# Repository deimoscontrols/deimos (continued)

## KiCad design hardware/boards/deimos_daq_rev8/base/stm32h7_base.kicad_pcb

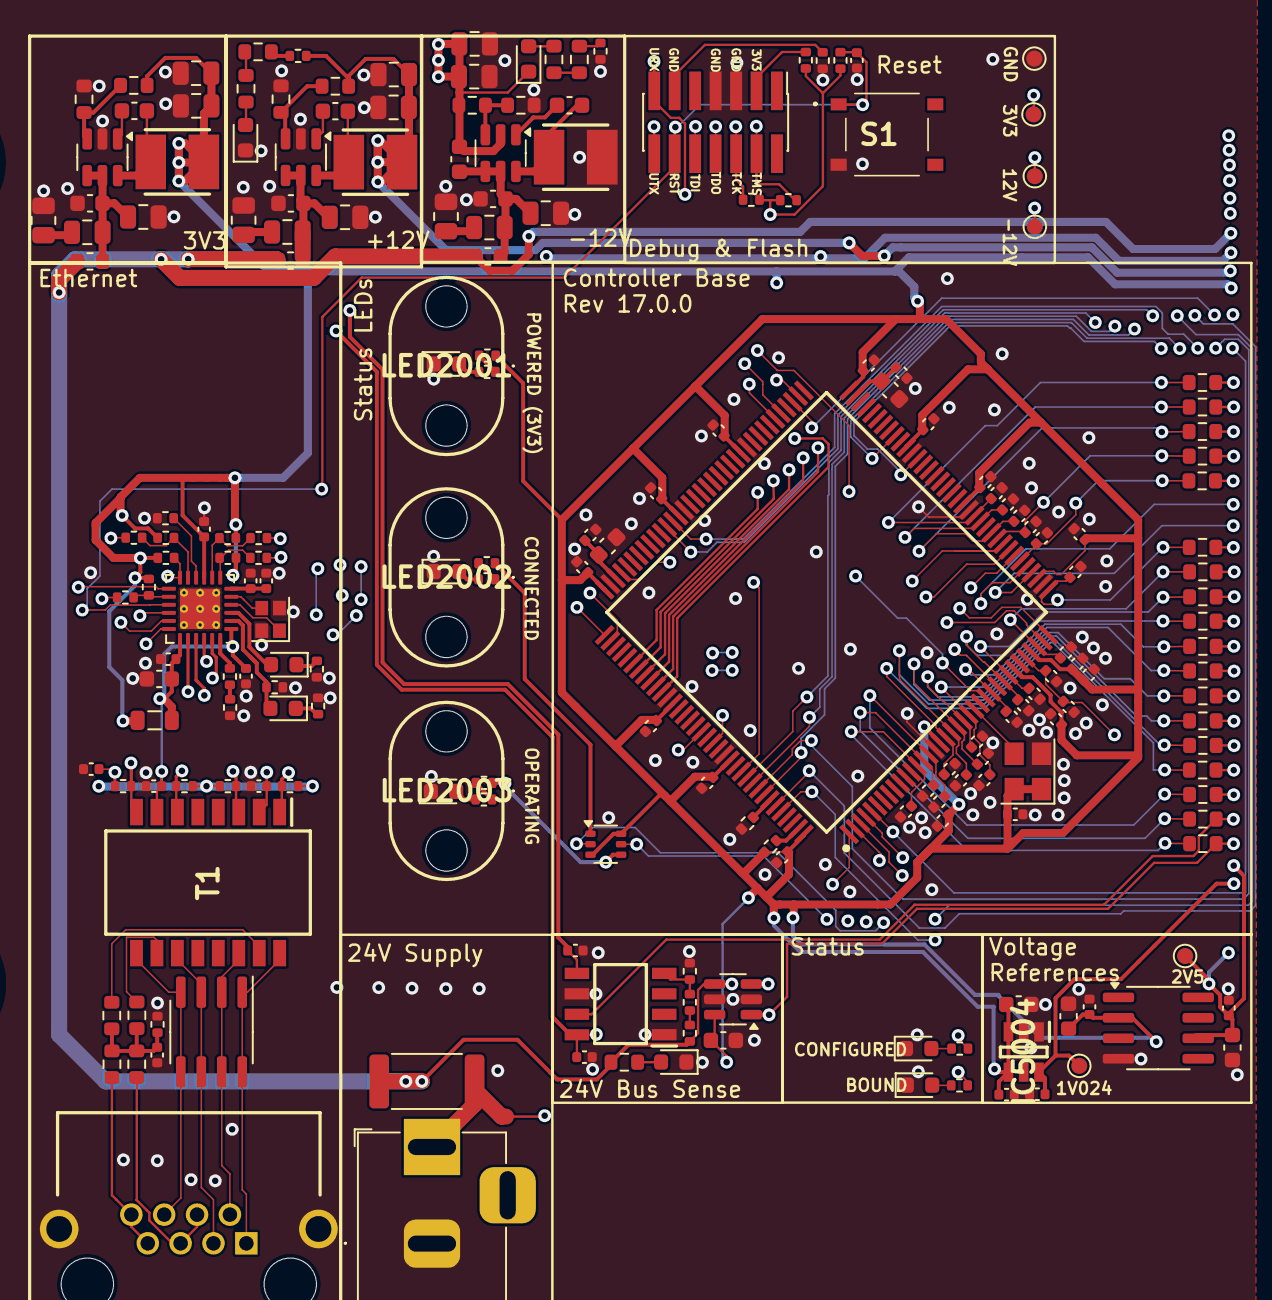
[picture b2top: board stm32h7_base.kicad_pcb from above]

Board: 4 copper layers, 202 parts (0 on the bottom side), 117 nets.

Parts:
C9, C10, C23, C5002, C5004, C6003: 10uF; C_0603_1608Metric
C11, C12, C13, C14, C15, C17, C18, C19, C22, C24, C26, C28, C29, C30, C31, C32, C33, C34, C35, C36, C37, C38, C39, C40, C4004, C5001, C5003, C5005, C6001, C6002: 0.1uF; C_0402_1005Metric
C16: 4.7nF; C_0402_1005Metric
C25: 470pF 0402; C_0402_1005Metric
C27, C44, C45, C46, C47, C48, C49, C50, C51, C52, C53, C54, C55, C56, C59, C60, C61, C62, C63: 1uF 0402; C_0402_1005Metric
C42, C43: 10nF; C_0402_1005Metric
C4001: 0.1uF 0603; C_0603_1608Metric
C4002, C4008, C4011, C7003, C9001, C9002, C10005: 0.1uF 50V 0603; C_0603_1608Metric
C4006, C4007, C4010, C7001, C7002, C7004, C9004, C10001, C10002: 10uF 50V 0805; C_0805_2012Metric
C4009, C9003, C10006: 2.2uF 50V 0805; C_0805_2012Metric
D2, D6, D36, D37, D38, D39, D2001, D2003, D2004, D2005: Purple LED; LED_0603_1608Metric
D5: CDNBS08-SLVU2.8-4; SOIC-8_3.9x4.9mm_P1.27mm
FB1: GZ2012D601TF; L_0805_2012Metric
H1001, H1002: MountingHole_for_10-32; MountingHole_5mm
IC1: STM32H743ZIT6; QFP50P2200X2200X160-144N
IC4001, IC10001, IC10002: TPS560430XDBVR; SOT-23-6
IC5004: REF35102QDBVR; SOT95P280X145-6N
IC8001: INA826AIDR; SOIC127P600X175-8N
J4: Conn_02x07_Odd_Even; PinHeader_2x07_P1.27mm_Vertical_SMD
J3001: RCH_RC01133; RCHRC01133
J8001: Barrel_Jack PJ-202BH; BarrelJack_Horizontal
L4001, L9001: 33uH FNR4020S330MT; INDPM4040X300N
L4002, L8001, L9002: 220nH 0603; L_0603_1608Metric
L7001: 12uH FNR4030S120MT; INDPM4040X300N
LED2001, LED2002, LED2003: SMFLP10.0; SMFLP100
R1, R2, R3, R4, R6, R27, R28, R29, R30, R31, R33, R49, R2007, R2008, R8006, R8007: 10k; R_0402_1005Metric
R5, R50: 1k; R_0402_1005Metric
R8, R9, R10, R11, R22, R32, R35, R36, R37, R38, R39, R40, R41, R44, R45, R46, R51, R52: 10R 0603; R_0603_1608Metric
R13, R14, R15, R16: 49.9; R_0402_1005Metric
R17, R18, R19, R20: 75; R_0603_1608Metric
R21: 1M; R_0402_1005Metric
R23, R26, R47, R48: 33R; R_0402_1005Metric
R34, R56, R8005: 1.5k; R_0402_1005Metric
R54: 12k; R_0402_1005Metric
R57: 100R; R_0402_1005Metric
R58, R2001, R2002, R2004, R2011, R2012, R2013, R2014: 100R 0402; R_0402_1005Metric
R2003, R4002, R9001: 243k 0603; R_0603_1608Metric
R2005, R2006, R2009, R2010, R4003, R9002, R10001: 22.1k 0603; R_0603_1608Metric
R4001, R10002, R10003: 1R 0805; R_0805_2012Metric
R7001: 51k 0603; R_0603_1608Metric
R8004: MRF6432(2512)LR006FTS 0.006 1%; R_2512_6332Metric
S1: TS-1187A-B-A-B; TS1187ABAB
T1: H1102NLT; SOIC127P940X622-16N
TP4001: TestPoint_GND_1; TestPoint_Pad_D1.0mm
TP10001, TP11001: TestPoint_+12V; TestPoint_Pad_D1.0mm
TP10003: TestPoint_+2V5; TestPoint_Pad_D1.0mm
TP10004: TestPoint_+3V3; TestPoint_Pad_D1.0mm
TP10005: TestPoint_+1V024; TestPoint_Pad_D1.0mm
U5: LAN8742A; VQFN-24-1EP_4x4mm_P0.5mm_EP2.5x2.5mm_ThermalVias
U2001: NTJD4001NT1G; SOT-363_SC-70-6
U4001: INA181A2; SOT-23-6
U6002: ADR4525; SOIC-8_3.9x4.9mm_P1.27mm
Y1: SiT1602BI-21-33S-48.000000; Crystal_SMD_3225-4Pin_3.2x2.5mm
Y2: NX2016SA-25.000M-STD-CZS-1; Crystal_SMD_2016-4Pin_2.0x1.6mm

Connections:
+1V024: C6001.1, IC5004.6 (VREF), TP10005.1
+2V5: C28.2, C43.2, C5003.2, C5004.2, IC1.32 (VREF+), TP10003.1, U6002.6 (OUT)
+3V3: C11.2, C12.2, C26.2, C29.2, C30.2, C31.2, C32.2, C33.2, C34.2, C35.2, C36.2, C37.2, C38.2, C39.2, C40.2, C42.2, C4001.1, C5001.2, C5002.2, C6002.2, C6003.2, C7004.1, C10006.1, FB1.1, IC1.17 (VDD_1), IC1.30 (VDD_2), IC1.33 (VDDA), IC1.39 (VDD_3), IC1.52 (VDD_4), IC1.62 (VDD_5), IC1.72 (VDD_6), IC1.84 (VDD_7), IC1.95 (VDD33USB), IC1.108 (VDD_8), IC1.121 (VDD_9), IC1.131 (VDD_10), IC1.144 (VDD_11), IC5004.3 (EN), IC5004.4 (VIN), L7001.1, R1.2, R2.1, R3.2, R6.1, R27.1, R28.1, R29.1, R49.1, R56.2, R2001.1, R2004.1, R7001.1, TP10004.1, U5.9 (VDDIO), U2001.3 (D2), U2001.6 (D1), U4001.6 (V+), U6002.2 (IN), Y1.1 (OE/~ST/NC), Y1.4 (VDD)
+12V: C4004.2, C9003.1, C9004.1, IC8001.8 (+VS), L9001.1, R2007.2, R9001.1, TP10001.1
+24V: L4002.2, L8001.2, L9002.2, R2003.2, R8004.1, R8006.1, U4001.4 (-)
-12V: C4009.1, C4010.1, C4011.1, C5005.2, D2005.1 (K), IC4001.2 (GND), IC8001.5 (-VS), R4003.2, TP11001.1
/AIN0: R8.1, U4001.1
/AIN1: IC8001.7 (VOUT), R9.1
/Micro/AIN0_Filt: C44.1, IC1.13 (PF3), R8.2
/Micro/AIN1_Filt: C45.1, IC1.14 (PF4), R9.2
/Micro/AIN2_Filt: C46.1, IC1.15 (PF5), R10.2
/Micro/AIN3_Filt: C47.1, IC1.18 (PF6), R11.2
/Micro/AIN4_Filt: C48.1, IC1.19 (PF7), R22.2
/Micro/AIN5_Filt: C49.1, IC1.20 (PF8), R32.2
/Micro/AIN6_Filt: C50.1, IC1.21 (PF9), R35.2
/Micro/AIN7_Filt: C51.1, IC1.22 (PF10), R36.2
/Micro/AIN8_Filt: C52.1, IC1.26 (PC0), R37.2
/Micro/AIN9_Filt: C53.1, IC1.28 (PC2_C), R38.2
/Micro/AIN10_Filt: C54.1, IC1.29 (PC3_C), R39.2
/Micro/AIN11_Filt: C55.1, IC1.34 (PA0), R40.2
/Micro/AIN12_Filt: C56.1, IC1.37 (PA3), R41.2
/Micro/AIN15_Filt: C59.1, IC1.42 (PA6), R44.2
/Micro/AIN16_Filt: C60.1, IC1.46 (PB0), R45.2
/Micro/AIN17_Filt: C61.1, IC1.47 (PB1), R46.2
/Micro/AIN18_Filt: C62.1, IC1.49 (PF11), R51.2
/Micro/AIN19_Filt: C63.1, IC1.50 (PF12), R52.2
/Micro/DEBUG_RESET: C19.2, IC1.25 (NRST), J4.12, R2.2, S1.A1 (COM_1), U5.15 (~RST)
/Micro/DEBUG_TCK/SWCLK: IC1.109 (PA14), J4.6, R1.1
/Micro/DEBUG_TDI: IC1.110 (PA15), J4.10
/Micro/DEBUG_TDO/SWO: IC1.133 (PB3), J4.8
/Micro/DEBUG_TMS/SWDIO: IC1.105 (PA13), J4.4, R3.1
/Micro/Ethernet/RX+: R14.1, T1.6 (RD+), U5.23 (RXP)
/Micro/Ethernet/RX-: R13.1, T1.8 (RD-), U5.22 (RXN)
/Micro/Ethernet/TX+: R16.1, T1.1 (TD+), U5.21 (TXP)
/Micro/Ethernet/TX-: R15.1, T1.3 (TD-), U5.20 (TXN)
/Micro/HSECLK: IC1.23 (PH0-OSC_IN), Y1.3 (OUT)
/Micro/LED0: IC1.4 (PE5), U2001.2 (G1)
/Micro/LED1: IC1.3 (PE4), R5.2
/Micro/LED2: IC1.2 (PE3), R50.2
/Micro/LED3: IC1.1 (PE2), U2001.5 (G2)
/Micro/RMII_CRS_DV: IC1.43 (PA7), R47.1
/Micro/RMII_MDC: IC1.27 (PC1), U5.13 (MDC)
/Micro/RMII_MDIO: IC1.36 (PA2), R56.1, U5.12 (MDIO)
/Micro/RMII_REF_CLK: IC1.35 (PA1), R48.2
/Micro/RMII_RXD0: IC1.44 (PC4), R26.2
/Micro/RMII_RXD1: IC1.45 (PC5), R23.2
/Micro/RMII_TXD0: IC1.128 (PG13), U5.17 (TXD0)
/Micro/RMII_TXD1: IC1.74 (PB13), U5.18 (TXD1)
/Micro/RMII_TX_EN: IC1.126 (PG11), U5.16 (TXEN)
/Micro/UART_RX: IC1.78 (PD9), J4.13
/Micro/UART_TX: IC1.77 (PD8), J4.14
GND: C9.1, C10.2, C11.1, C12.1, C13.1, C14.1, C15.1, C16.2, C17.1, C18.1, C19.1, C22.1, C23.1, C24.1, C25.1, C26.1, C27.1, C28.1, C29.1, C30.1, C31.1, C32.1, C33.1, C34.1, C35.1, C36.1, C37.1, C38.1, C39.1, C40.1, C42.1, C43.1, C44.2, C45.2, C46.2, C47.2, C48.2, C49.2, C50.2, C51.2, C52.2, C53.2, C54.2, C55.2, C56.2, C59.2, C60.2, C61.2, C62.2, C63.2, C4001.2, C4002.2, C4004.1, C4007.2, C4009.2, C4010.2, C5001.1, C5002.1, C5003.1, C5004.1, C5005.1, C6001.2, C6002.1, C6003.1, C7002.2, C7004.2, C9001.2, C9003.2, C9004.2, C10002.2, C10005.2, C10006.2, D6.1 (K), D37.1 (K), D38.1 (K), D39.1 (K), D2001.1 (K), D2003.1 (K), D2004.1 (K), IC1.16 (VSS_1), IC1.31 (VSSA), IC1.38 (VSS_2), IC1.51 (VSS_3), IC1.61 (VSS_4), IC1.83 (VSS_5), IC1.94 (VSS_6), IC1.107 (VSS_7), IC1.120 (VSS_8), IC1.130 (VSS_9), IC5004.1 (GND_1), IC5004.2 (GND_2), IC8001.1 (-IN1), IC8001.6 (REF), IC10001.2 (GND), IC10002.2 (GND), J4.5, J4.7, J3001.9 (MH1), J3001.10 (MH2), J8001.2, L4001.2, R4.2, R21.2, R30.1, R31.2, R33.2, R34.1, R57.1, R58.1, R2008.2, R4001.2, R4002.1, R8005.1, R9002.2, R10001.2, R10002.2, R10003.2, S1.C1 (NO_1), TP4001.1, U5.25 (VSS), U4001.2 (GND), U4001.5 (REF), U6002.4 (GND), Y1.2 (GND), Y2.2 (GND_1), Y2.4 (GND_2)
unnamed: C16.1, R17.2, R18.1, R19.1, R20.2, R21.1
unnamed: C4006.2, R4001.1
unnamed: C7001.2, R10003.1
unnamed: C10001.2, R10002.1
unnamed: D2.2 (A), U5.3 (LED1/REGOFF)
unnamed: D2.1 (K), R31.1
unnamed: D6.2 (A), R5.1
unnamed: D36.2 (A), R33.1, U5.2 (LED2/~INTSEL)
unnamed: D36.1 (K), R34.2
unnamed: D37.2 (A), R50.1
unnamed: D38.2 (A), R2014.2
unnamed: D39.2 (A), R2012.2
unnamed: D2001.2 (A), R2002.2
unnamed: D2003.2 (A), R2005.1
unnamed: D2004.2 (A), R2003.1
unnamed: D2005.2 (A), R2010.1
unnamed: IC1.138 (BOOT0), R4.1
unnamed: IC1.143 (PDR_ON), R6.2
unnamed: C9.2, C18.2, IC1.71 (VCAP_1)
unnamed: C10.1, C17.2, IC1.106 (VCAP_2)
unnamed: C4008.1, IC4001.1 (CB)
unnamed: C4002.1, C4006.1, C4007.1, C4011.2, IC4001.4 (EN), IC4001.5 (VIN), L4002.1
unnamed: IC4001.3 (FB), R4002.2, R4003.1
unnamed: C4008.2, IC4001.6 (SW), L4001.1
unnamed: IC8001.4 (+IN), R8005.2, R8007.1
unnamed: C7003.2, IC10001.1 (CB)
unnamed: C7001.1, C7002.1, C10005.1, IC10001.4 (EN), IC10001.5 (VIN), L8001.1
unnamed: IC10001.3 (FB), R7001.2, R10001.1
unnamed: C7003.1, IC10001.6 (SW), L7001.2
unnamed: C9002.2, IC10002.1 (CB)
unnamed: C9001.1, C10001.1, C10002.1, IC10002.4 (EN), IC10002.5 (VIN), L9002.1
unnamed: IC10002.3 (FB), R9001.2, R9002.1
unnamed: C9002.1, IC10002.6 (SW), L9001.2
unnamed: J4.3, R2001.2
unnamed: J4.11, R58.2
unnamed: J3001.4, J3001.5, R19.2
unnamed: J3001.7, J3001.8, R20.1
unnamed: R54.1, R57.2
unnamed: R2002.1, R2004.2
unnamed: R2005.2, R2006.2
unnamed: R2006.1, R2007.1
unnamed: R2008.1, R2009.1
unnamed: R2009.2, R2010.2
unnamed: R2011.2, R2012.1
unnamed: R2013.2, R2014.1
unnamed: R8006.2, R8007.2
unnamed: C13.2, C14.2, C15.2, C22.2, C23.2, C24.2, FB1.2, R13.2, R14.2, R15.2, R16.2, T1.2 (CT_1), T1.7 (CT_2), U5.1 (VDD2A), U5.19 (VDD1A)
unnamed: R17.1, T1.10 (NC_3)
unnamed: R18.2, T1.15 (NC_6)
unnamed: D5.3 (TVS1), D5.6 (TVS2), J3001.3, T1.11 (RX+)
unnamed: D5.4 (TVS2), D5.5 (TVS1), J3001.6, T1.9 (RX-)
unnamed: D5.1 (TVS1), D5.8 (TVS2), J3001.1, T1.16 (TX+)
unnamed: D5.2 (TVS2), D5.7 (TVS1), J3001.2, T1.14 (TX-)
unnamed: R28.2, R47.2, U5.11 (CRS_DV/MODE2)
unnamed: R54.2, U5.24 (RBIAS)
unnamed: R26.1, R49.2, U5.8 (RXD0/MODE0)
unnamed: R23.1, R27.2, U5.7 (RXD1/MODE1)
unnamed: R30.2, U5.10 (RXER/PHYAD0)
unnamed: C25.2, C27.2, U5.6 (VDDCR)
unnamed: U5.5 (XTAL1/CLKIN), Y2.3 (CRYSTAL_2)
unnamed: U5.4 (XTAL2), Y2.1 (CRYSTAL_1)
unnamed: R29.2, R48.1, U5.14 (~INT/REFCLKO)
unnamed: R2011.1, U2001.1 (S1)
unnamed: R2013.1, U2001.4 (S2)
unnamed: J8001.1, R8004.2, U4001.3 (+)

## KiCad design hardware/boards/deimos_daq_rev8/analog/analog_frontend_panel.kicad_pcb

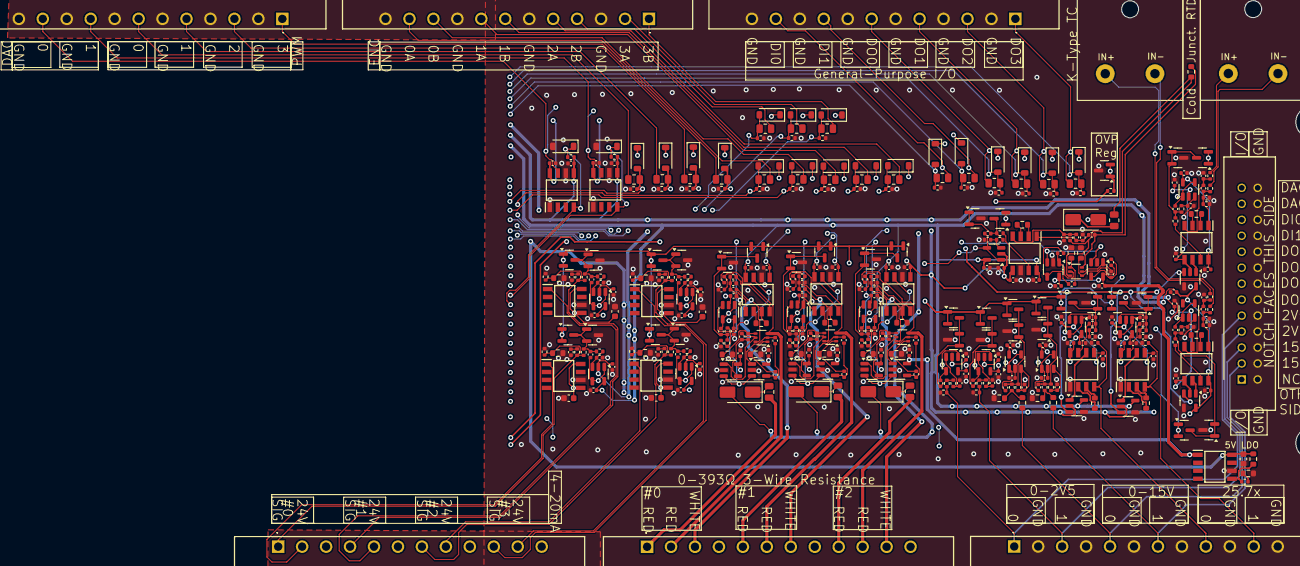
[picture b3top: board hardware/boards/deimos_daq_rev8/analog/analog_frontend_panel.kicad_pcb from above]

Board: 4 copper layers, 379 parts (0 on the bottom side), 202 nets.

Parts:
C1, C3, C7, C9, C49, C51, C60, C62, C71, C73, C82, C84: 2.2uF; C_0402_1005Metric
C2, C8, C50, C61, C72, C83: 1uF; C_0402_1005Metric
C4, C10, C52, C55, C58, C63, C66, C69, C74, C77, C80, C85, C88, C91, C5003, C5004, C6001, C7001, C8003, C8004, C9003, C9004, C14001, C14002, C15003, C15004, C16003, C16004, C17003, C17004, C18003, C18004, C20003, C20004, C21003, C21004, C24003, C24004, C25003, C25004, C28001, C28002, C28005, C28006, C30003, C30004, C31001, C31002, C31003, C32006, C33007, C34002, C37001, C39003, C42002, C42003, C44004, C45002, C46001, C47001: 0.1uF; C_0402_1005Metric
C25, C28, C31, C34, C44005, C44006, C45003, C45004, C46002, C46003, C47002, C47003: 10nF; C_0402_1005Metric
C1001, C10001, C11001, C12001, C13001: 0.1uF 50V 0603; C_0603_1608Metric
C5001, C5002, C8001, C8002, C9001, C9002, C15001, C15002, C16001, C16002, C17001, C17002, C18001, C18002, C20001, C20002, C21001, C21002, C24001, C24002, C25001, C25002, C28003, C28004, C30001, C30002, C32002, C32003, C33002, C33003, C44001, C44002: 10nF C0G 5%; C_0402_1005Metric
D7, D8, D9, D10: D_Schottky; D_SMA
D19001, D26001, D27001, D29002, D34001, D36002, D37001, D38002, D39003, D40003, D41001, D42002, D43001, D45002, D46001, D47001, D49001, D50001, D51002, D52002: B5819W SL; D_SOD-123
H1001, H1002: MountingHole_for_10-32; MountingHole_5mm
IC1, IC2, IC12, IC15, IC18, IC21, IC14001, IC31001, IC34002, IC37001: INA826AIDR; SOIC127P600X175-8N
IC13, IC14, IC16, IC17, IC19, IC20, IC22, IC23: TLV333IDBVR; SOT-23-5
IC1002, IC32001, IC33001, IC34001, IC35001: BD42540FJ-CE2; SOIC127P600X175-8N
J12, J13: AM-K-PCB
J1001, J1002, J1003, J1004, J1005, J1007: WJ15EDGRM-3.81-12P
J1006: XG4C-2631; SHDR26W70P254_2X13_4030X820X900P
Q5001, Q5002, Q8001, Q8002, Q9001, Q9002, Q15001, Q15002, Q16001, Q16002, Q17001, Q17002, Q18001, Q18002, Q20001, Q20002, Q21001, Q21002, Q24001, Q24002, Q25001, Q25002, Q28001, Q28002, Q28003, Q28004, Q30001, Q30002, Q31001, Q31002, Q42001, Q42002: MMBFJ113; SOT-23
R1: PTS060301B100RP100; R_0603_1608Metric
R2, R3, R7, R8: 10; R_0402_1005Metric
R4, R9, R10001, R11001, R12001, R13001, R14002, R19001, R22001, R26001, R27001, R27003, R29002, R31002, R33003, R36002, R38002, R39002, R39004, R40002, R42002, R45006, R46003, R47003, R49001, R50001, R51002, R52002: 1M; R_0402_1005Metric
R6, R11, R40, R49, R58, R67, R14001, R23002, R31001, R45003: RNCF0603TKY2K00 2k 0.01% 5ppm/C; R_0603_1608Metric
R22, R24, R26, R28: 200R; R_0402_1005Metric
R23, R25, R27, R29: RNCF0603TKY75R0 75R 0.01% 5ppm/C; R_0603_1608Metric
R41, R50, R59, R68: 300; R_0805_2012Metric
R42, R43, R51, R52, R60, R61, R69, R70: 10; C_0402_1005Metric
R44, R47, R53, R56, R62, R65, R71, R74, R23001, R45004: RNCF0603TKW10K0 10k 0.01% 5ppm/C; R_0603_1608Metric
R1001, R5001, R5002, R8001, R8002, R9001, R9002, R28001, R28002: 10k 1%; R_0402_1005Metric
R1002: 51k 0603; R_0603_1608Metric
R1003: 243k 0603; R_0603_1608Metric
R1004, R15001, R15002, R16001, R16002, R17001, R17002, R18001, R18002, R21001, R21002, R24001, R24002, R25001, R25002, R30001, R30002, R32001, R32002, R33001, R33002, R33005, R40003, R44001, R44002: 3.3k 1%; R_0402_1005Metric
R19002, R26002, R27002, R33004, R46004, R47004, R49002, R50002: 49.9; R_0805_2012Metric
R20001, R20002: 100k 1%; R_0402_1005Metric
R29001, R36001, R38001, R39001, R39003, R40001, R42001, R45005, R51001, R52001: 22k; R_0805_2012Metric
R44003, R44004, R45001, R45002, R46001, R46002, R47001, R47002: 10k 1%; C_0402_1005Metric
U1, U2, U3, U4: NTJD4001NT1G; SOT-363_SC-70-6
U1001: ATL431BQDBZR; SOT-23
U5001, U6001, U7001, U8001, U9001, U14001, U15001, U16001, U17001, U18001, U20002, U21001, U24001, U25001, U28001, U28002, U30001, U31001, U35001, U42002: OPA196xDBV; SOT-23-5

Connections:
2V5_OVP: Q5001.1 (D), Q5001.2 (S), Q8001.1 (D), Q8001.2 (S), Q9001.1 (D), Q9001.2 (S), Q15001.1 (D), Q15001.2 (S), Q16001.1 (D), Q16001.2 (S), Q17001.1 (D), Q17001.2 (S), Q18001.1 (D), Q18001.2 (S), Q20001.1 (D), Q20001.2 (S), Q21001.1 (D), Q21001.2 (S), Q24001.1 (D), Q24001.2 (S), Q25001.1 (D), Q25001.2 (S), Q28001.1 (D), Q28001.2 (S), Q28003.1 (D), Q28003.2 (S), Q30001.1 (D), Q30001.2 (S), Q31001.1 (D), Q31001.2 (S), Q42001.1 (D), Q42001.2 (S), R1004.1, U1001.1 (K), U1001.2 (REF)
+1V024: U6001.3 (+), U7001.3 (+), U14001.3 (+), U35001.3 (+)
+2V5: IC13.3 (+IN), IC14.3 (+IN), IC16.3 (+IN), IC17.3 (+IN), IC19.3 (+IN), IC20.3 (+IN), IC22.3 (+IN), IC23.3 (+IN)
+3V3: D7.2 (A), D8.2 (A), D9.2 (A), D10.2 (A), D19001.1 (K), D26001.1 (K), D27001.1 (K), D29002.1 (K), D36002.1 (K), D37001.1 (K), D38002.1 (K), D39003.1 (K), D40003.1 (K), D42002.1 (K), D43001.1 (K), D45002.1 (K), D46001.1 (K), D47001.1 (K), D49001.1 (K), D50001.1 (K), D51002.1 (K), D52002.1 (K), R1004.2
+5V: C55.1, C58.1, C66.1, C69.1, C77.1, C80.1, C88.1, C91.1, IC13.5 (V+), IC14.5 (V+), IC16.5 (V+), IC17.5 (V+), IC19.5 (V+), IC20.5 (V+), IC22.5 (V+), IC23.5 (V+), IC1002.1 (VO)
+12V: C4.1, C10.1, C52.1, C63.1, C74.1, C85.1, C5003.2, C8003.2, C9003.2, C14001.2, C15003.2, C16003.2, C17003.2, C18003.2, C20003.2, C21003.2, C24003.2, C25003.2, C28001.2, C28005.2, C30003.2, C31001.2, C31002.2, C34002.2, C37001.2, C42002.2, IC1.8 (+VS), IC2.8 (+VS), IC12.8 (+VS), IC15.8 (+VS), IC18.8 (+VS), IC21.8 (+VS), IC14001.8 (+VS), IC31001.8 (+VS), IC34002.8 (+VS), IC37001.8 (+VS), U5001.5 (V+), U6001.5 (V+), U7001.5 (V+), U8001.5 (V+), U9001.5 (V+), U14001.5 (V+), U15001.5 (V+), U16001.5 (V+), U17001.5 (V+), U18001.5 (V+), U20002.5 (V+), U21001.5 (V+), U24001.5 (V+), U25001.5 (V+), U28001.5 (V+), U28002.5 (V+), U30001.5 (V+), U31001.5 (V+), U35001.5 (V+), U42002.5 (V+)
+24V: C1001.2, C10001.2, C11001.2, C12001.2, C13001.2, IC1002.8 (VCC), IC32001.5 (ADJ_/_EN), IC32001.8 (VCC), IC33001.5 (ADJ_/_EN), IC33001.8 (VCC), IC34001.5 (ADJ_/_EN), IC34001.8 (VCC), IC35001.5 (ADJ_/_EN), IC35001.8 (VCC), R1003.2
-12V: C5004.2, C6001.2, C7001.2, C8004.2, C9004.2, C14002.2, C15004.2, C16004.2, C17004.2, C18004.2, C20004.2, C21004.2, C24004.2, C25004.2, C28002.2, C28006.2, C30004.2, C31003.2, C32006.2, C33007.2, C39003.2, C42003.2, C44004.1, C45002.1, C46001.1, C47001.1, IC1.5 (-VS), IC2.5 (-VS), IC12.5 (-VS), IC15.5 (-VS), IC18.5 (-VS), IC21.5 (-VS), IC14001.5 (-VS), IC31001.5 (-VS), IC34002.5 (-VS), IC37001.5 (-VS), R33005.1, R40003.1, U5001.2 (V-), U6001.2 (V-), U7001.2 (V-), U8001.2 (V-), U9001.2 (V-), U14001.2 (V-), U15001.2 (V-), U16001.2 (V-), U17001.2 (V-), U18001.2 (V-), U20002.2 (V-), U21001.2 (V-), U24001.2 (V-), U25001.2 (V-), U28001.2 (V-), U28002.2 (V-), U30001.2 (V-), U31001.2 (V-), U35001.2 (V-), U42002.2 (V-)
/2p5V_0: J1003.1, J1006.9, R21001.1, R27003.1
/2p5V_1: J1003.3, J1006.7, R22001.1, R25001.1
/4-20mA Frontend1/+24_EXC: IC33001.1 (VO), J1004.5
/4-20mA Frontend1/SIGNAL: J1004.4, R24.2, R25.2, R11001.1, R30001.1
/4-20mA Frontend2/+24_EXC: IC34001.1 (VO), J1004.8
/4-20mA Frontend2/SIGNAL: J1004.7, R26.2, R27.2, R12001.1, R32001.1
/4-20mA Frontend3/+24_EXC: IC35001.1 (VO), J1004.11
/4-20mA Frontend3/SIGNAL: J1004.10, R28.2, R29.2, R13001.1, R33001.1
/4-20mA Frontend/+24_EXC: IC32001.1 (VO), J1004.2
/4-20mA Frontend/SIGNAL: J1004.1, R22.2, R23.2, R10001.1, R16001.1
/15V_0: J1003.5, J1006.5, R45004.2
/15V_1: J1003.7, J1006.3, R23001.2
/25p7x_0: IC31001.4 (+IN), J1003.9, R31002.1
/25p7x_1: IC14001.4 (+IN), J1003.11, R14002.1
/AIN2: C20002.2, U20002.1, U20002.4 (-)
/AIN3: C16002.2, U16001.1, U16001.4 (-)
/AIN4: C30002.2, U28001.1, U28001.4 (-)
/AIN5: C32003.2, U30001.1, U30001.4 (-)
/AIN6: C33003.2, U31001.1, U31001.4 (-)
/AIN7: C15002.2, U15001.1, U15001.4 (-)
/AIN8: C17002.2, U17001.1, U17001.4 (-)
/AIN9: C18002.2, U18001.1, U18001.4 (-)
/AIN10: C5002.2, U5001.1, U5001.4 (-)
/AIN11: C8002.2, U8001.1, U8001.4 (-)
/AIN12: C21002.2, U21001.1, U21001.4 (-)
/AIN13_DAC0: D41001.1 (K), IC37001.4 (+IN), R40003.2
/AIN14_DAC1: D34001.1 (K), IC34002.4 (+IN), R33005.2
/AIN15: C25002.2, U25001.1, U25001.4 (-)
/AIN16: C44002.2, U42002.1, U42002.4 (-)
/AIN17: C24002.2, U24001.1, U24001.4 (-)
/AIN18: C9002.2, U9001.1, U9001.4 (-)
/AIN19: C28004.2, U28002.1, U28002.4 (-)
/DAC0: IC37001.7 (VOUT), J1002.11, J1006.25
/DAC1: IC34002.7 (VOUT), J1002.9, J1006.23
/DI0: D29002.2 (A), R29001.2, R29002.1
/DI0_CONN: J1006.21, J1007.11, R29001.1
/DI1: D45002.2 (A), R45005.2, R45006.1
/DI1_CONN: J1006.19, J1007.9, R45005.1
/DO0: D46001.2 (A), R46003.1, R46004.1
/DO0_CONN: J1006.17, J1007.7, R46004.2
/DO1: D47001.2 (A), R47003.1, R47004.1
/DO1_CONN: J1006.15, J1007.5, R47004.2
/DO2: D49001.2 (A), R49001.1, R49002.1
/DO2_CONN: J1006.13, J1007.3, R49002.2
/DO3: D50001.2 (A), R50001.1, R50002.1
/DO3_CONN: J1006.11, J1007.1, R50002.2
/ENCODER0_A: D38002.2 (A), R38001.2, R38002.1
/ENCODER0_B: D43001.2 (A), R39001.2, R39002.1
/ENCODER1_A: D42002.2 (A), R42001.2, R42002.1
/ENCODER1_B: D40003.2 (A), R40001.2, R40002.1
/ENCODER2_A: D39003.2 (A), R39003.2, R39004.1
/ENCODER2_B: D36002.2 (A), R36001.2, R36002.1
/ENCODER3_A: D51002.2 (A), R51001.2, R51002.1
/ENCODER3_B: D52002.2 (A), R52001.2, R52002.1
/K-Type TC Amp1/Signal+: C7.1, C8.1, IC2.4 (+IN), R7.2
/K-Type TC Amp1/Signal-: C8.2, C9.1, IC2.1 (-IN1), R8.1, R9.1
/K-Type TC Amp1/sallen_key_1kHz/VIN: IC2.7 (VOUT), R8001.1
/K-Type TC Amp/Signal+: C1.1, C2.1, IC1.4 (+IN), R2.2
/K-Type TC Amp/Signal-: C2.2, C3.1, IC1.1 (-IN1), R3.1, R4.1
/K-Type TC Amp/sallen_key_1kHz/VIN: IC1.7 (VOUT), R5001.1
/PWM0: D37001.2 (A), R33003.1, R33004.1
/PWM1: D19001.2 (A), R19001.1, R19002.1
/PWM2: D26001.2 (A), R26001.1, R26002.1
/PWM3: D27001.2 (A), R27001.1, R27002.1
/RTD Amp1/R+: J1005.5, R59.2
/RTD Amp1/R-: J1005.6, R60.2, U3.3 (D2)
/RTD Amp1/W-: J1005.7, R61.2, U3.6 (D1)
/RTD Amp1/rtd_amp_inner/Signal+: C71.2, C72.1, IC18.4 (+IN), R60.1
/RTD Amp1/rtd_amp_inner/Signal-: C72.2, C73.1, IC18.1 (-IN1), R61.1
/RTD Amp1/rtd_amp_inner/Vout: IC18.7 (VOUT), R17001.1
/RTD Amp2/R+: J1005.9, R68.2
/RTD Amp2/R-: J1005.10, R69.2, U4.3 (D2)
/RTD Amp2/W-: J1005.11, R70.2, U4.6 (D1)
/RTD Amp2/rtd_amp_inner/Signal+: C82.2, C83.1, IC21.4 (+IN), R69.1
/RTD Amp2/rtd_amp_inner/Signal-: C83.2, C84.1, IC21.1 (-IN1), R70.1
/RTD Amp2/rtd_amp_inner/Vout: IC21.7 (VOUT), R18001.1
/RTD Amp/R+: J1005.1, R41.2
/RTD Amp/R-: J1005.2, R42.2, U1.3 (D2)
/RTD Amp/W-: J1005.3, R43.2, U1.6 (D1)
/RTD Amp/rtd_amp_inner/Signal+: C49.2, C50.1, IC12.4 (+IN), R42.1
/RTD Amp/rtd_amp_inner/Signal-: C50.2, C51.1, IC12.1 (-IN1), R43.1
/RTD Amp/rtd_amp_inner/Vout: IC12.7 (VOUT), R15001.1
/ain_0-15V_1/sallen_key_3kHz8/VIN: R23001.1, R23002.1, R24001.1
/ain_0-15V_/sallen_key_3kHz8/VIN: R44001.1, R45003.1, R45004.1
/ain_g25p7_1/sallen_key_1kHz2/VIN: IC14001.7 (VOUT), R28001.1
/ain_g25p7_/sallen_key_1kHz2/VIN: IC31001.7 (VOUT), R9001.1
/pwm_in_buf1/VIN: J1001.11, R38001.1
/pwm_in_buf2/VIN: J1001.5, R39003.1
/pwm_in_buf3/VIN: J1001.7, R40001.1
/pwm_in_buf4/VIN: J1001.8, R42001.1
/pwm_in_buf5/VIN: J1001.4, R36001.1
/pwm_in_buf8/VIN: J1001.2, R51001.1
/pwm_in_buf9/VIN: J1001.1, R52001.1
/pwm_in_buf/VIN: J1001.10, R39001.1
/pwm_out_buf1/VOUT: J1002.5, R19002.2
/pwm_out_buf2/VOUT: J1002.3, R26002.2
/pwm_out_buf3/VOUT: J1002.1, R27002.2
/pwm_out_buf/VOUT: J1002.7, R33004.2
/rtd_amp_inner1/250uA_SINK_1: R1.1, R52.2, U2.6 (D1)
/rtd_amp_inner1/250uA_SINK_2: R1.2, R50.2, R51.2, U2.3 (D2)
/rtd_amp_inner1/Signal+: C60.2, C61.1, IC15.4 (+IN), R51.1
/rtd_amp_inner1/Signal-: C61.2, C62.1, IC15.1 (-IN1), R52.1
/rtd_amp_inner1/Vout: IC15.7 (VOUT), R20002.2
GND: C1.2, C3.2, C4.2, C7.2, C9.2, C10.2, C25.2, C28.2, C31.2, C34.2, C49.1, C51.2, C52.2, C55.2, C58.2, C60.1, C62.2, C63.2, C66.2, C69.2, C71.1, C73.2, C74.2, C77.2, C80.2, C82.1, C84.2, C85.2, C88.2, C91.2, C1001.1, C5001.1, C5003.1, C5004.1, C6001.1, C7001.1, C8001.1, C8003.1, C8004.1, C9001.1, C9003.1, C9004.1, C10001.1, C11001.1, C12001.1, C13001.1, C14001.1, C14002.1, C15001.1, C15003.1, C15004.1, C16001.1, C16003.1, C16004.1, C17001.1, C17003.1, C17004.1, C18001.1, C18003.1, C18004.1, C20001.1, C20003.1, C20004.1, C21001.1, C21003.1, C21004.1, C24001.1, C24003.1, C24004.1, C25001.1, C25003.1, C25004.1, C28001.1, C28002.1, C28003.1, C28005.1, C28006.1, C30001.1, C30003.1, C30004.1, C31001.1, C31002.1, C31003.1, C32002.1, C32006.1, C33002.1, C33007.1, C34002.1, C37001.1, C39003.1, C42002.1, C42003.1, C44001.1, C44004.2, C45002.2, C46001.2, C47001.2, D34001.2 (A), D41001.2 (A), IC12.6 (REF), IC13.2 (V-), IC14.2 (V-), IC15.6 (REF), IC16.2 (V-), IC17.2 (V-), IC18.6 (REF), IC19.2 (V-), IC20.2 (V-), IC21.6 (REF), IC22.2 (V-), IC23.2 (V-), IC1002.6 (GND), IC14001.1 (-IN1), IC31001.1 (-IN1), IC32001.6 (GND), IC33001.6 (GND), IC34001.6 (GND), IC34002.1 (-IN1), IC34002.6 (REF), IC35001.6 (GND), IC37001.1 (-IN1), IC37001.6 (REF), J1001.3, J1001.6, J1001.9, J1001.12, J1002.2, J1002.4, J1002.6, J1002.8, J1002.10, J1002.12, J1003.2, J1003.4, J1003.6, J1003.8, J1003.10, J1003.12, J1006.2, J1006.4, J1006.6, J1006.8, J1006.10, J1006.12, J1006.14, J1006.16, J1006.18, J1006.20, J1006.22, J1006.24, J1006.26, J1007.2, J1007.4, J1007.6, J1007.8, J1007.10, J1007.12, Q5002.3 (G), Q8002.3 (G), Q9002.3 (G), Q15002.3 (G), Q16002.3 (G), Q17002.3 (G), Q18002.3 (G), Q20002.3 (G), Q21002.3 (G), Q24002.3 (G), Q25002.3 (G), Q28002.3 (G), Q28004.3 (G), Q30002.3 (G), Q31002.3 (G), Q42002.3 (G), R4.2, R9.2, R23.1, R25.1, R27.1, R29.1, R44.2, R47.2, R53.2, R56.2, R62.2, R65.2, R71.2, R74.2, R1002.1, R10001.2, R11001.2, R12001.2, R13001.2, R14002.2, R19001.2, R22001.2, R23002.2, R26001.2, R27001.2, R27003.2, R29002.2, R31002.2, R33003.2, R36002.2, R38002.2, R39002.2, R39004.2, R40002.2, R42002.2, R45003.2, R45006.2, R46003.2, R47003.2, R49001.2, R50001.2, R51002.2, R52002.2, U1001.3 (A), U6001.4 (-), U7001.4 (-), U14001.4 (-), U35001.4 (-)
unnamed: C25.1, R22.1
unnamed: C28.1, R24.1
unnamed: C31.1, R26.1
unnamed: C34.1, R28.1
unnamed: D7.1 (K), R41.1
unnamed: D8.1 (K), R50.1
unnamed: D9.1 (K), R59.1
unnamed: D10.1 (K), R68.1
unnamed: IC1.6 (REF), U6001.1
unnamed: IC1.2 (RG_1), R6.1
unnamed: IC1.3 (RG_2), R6.2
unnamed: IC2.6 (REF), U7001.1
unnamed: IC2.2 (RG_1), R11.1
unnamed: IC2.3 (RG_2), R11.2
unnamed: IC12.2 (RG_1), R40.1
unnamed: IC12.3 (RG_2), R40.2
unnamed: C45003.1, IC13.4 (-IN), R45001.2
unnamed: C45003.2, IC13.1 (OUT), U1.2 (G1)
unnamed: C45004.1, IC14.4 (-IN), R45002.1
unnamed: C45004.2, IC14.1 (OUT), U1.5 (G2)
unnamed: IC15.2 (RG_1), R49.1
unnamed: IC15.3 (RG_2), R49.2
unnamed: C44005.1, IC16.4 (-IN), R44003.2
unnamed: C44005.2, IC16.1 (OUT), U2.2 (G1)
unnamed: C44006.1, IC17.4 (-IN), R44004.1
unnamed: C44006.2, IC17.1 (OUT), U2.5 (G2)
unnamed: IC18.2 (RG_1), R58.1
unnamed: IC18.3 (RG_2), R58.2
unnamed: C46002.1, IC19.4 (-IN), R46001.2
unnamed: C46002.2, IC19.1 (OUT), U3.2 (G1)
unnamed: C46003.1, IC20.4 (-IN), R46002.1
unnamed: C46003.2, IC20.1 (OUT), U3.5 (G2)
unnamed: IC21.2 (RG_1), R67.1
unnamed: IC21.3 (RG_2), R67.2
unnamed: C47002.1, IC22.4 (-IN), R47001.2
unnamed: C47002.2, IC22.1 (OUT), U4.2 (G1)
unnamed: C47003.1, IC23.4 (-IN), R47002.1
unnamed: C47003.2, IC23.1 (OUT), U4.5 (G2)
unnamed: IC1002.5 (ADJ_/_EN), R1001.1, R1003.1
unnamed: IC14001.6 (REF), U14001.1
unnamed: IC14001.2 (RG_1), R14001.1
unnamed: IC14001.3 (RG_2), R14001.2
unnamed: IC31001.6 (REF), U35001.1
unnamed: IC31001.2 (RG_1), R31001.1
unnamed: IC31001.3 (RG_2), R31001.2
unnamed: J12.1, R3.2
unnamed: J12.2, R2.1
unnamed: J13.1, R8.2
unnamed: J13.2, R7.1
unnamed: C5002.1, Q5001.3 (G), Q5002.1 (D), Q5002.2 (S), R5001.2, R5002.1
unnamed: C8002.1, Q8001.3 (G), Q8002.1 (D), Q8002.2 (S), R8001.2, R8002.1
unnamed: C9002.1, Q9001.3 (G), Q9002.1 (D), Q9002.2 (S), R9001.2, R9002.1
unnamed: C15002.1, Q15001.3 (G), Q15002.1 (D), Q15002.2 (S), R15001.2, R15002.1
unnamed: C16002.1, Q16001.3 (G), Q16002.1 (D), Q16002.2 (S), R16001.2, R16002.1
unnamed: C17002.1, Q17001.3 (G), Q17002.1 (D), Q17002.2 (S), R17001.2, R17002.1
unnamed: C18002.1, Q18001.3 (G), Q18002.1 (D), Q18002.2 (S), R18001.2, R18002.1
unnamed: C20002.1, Q20001.3 (G), Q20002.1 (D), Q20002.2 (S), R20001.2, R20002.1
unnamed: C21002.1, Q21001.3 (G), Q21002.1 (D), Q21002.2 (S), R21001.2, R21002.1
unnamed: C24002.1, Q24001.3 (G), Q24002.1 (D), Q24002.2 (S), R24001.2, R24002.1
unnamed: C25002.1, Q25001.3 (G), Q25002.1 (D), Q25002.2 (S), R25001.2, R25002.1
unnamed: C30002.1, Q28001.3 (G), Q28002.1 (D), Q28002.2 (S), R30001.2, R30002.1
unnamed: C28004.1, Q28003.3 (G), Q28004.1 (D), Q28004.2 (S), R28001.2, R28002.1
unnamed: C32003.1, Q30001.3 (G), Q30002.1 (D), Q30002.2 (S), R32001.2, R32002.1
unnamed: C33003.1, Q31001.3 (G), Q31002.1 (D), Q31002.2 (S), R33001.2, R33002.1
unnamed: C44002.1, Q42001.3 (G), Q42002.1 (D), Q42002.2 (S), R44001.2, R44002.1
unnamed: R1001.2, R1002.2
unnamed: R44.1, R45001.1, U1.1 (S1)
unnamed: R47.1, R45002.2, U1.4 (S2)
unnamed: R53.1, R44003.1, U2.1 (S1)
unnamed: R56.1, R44004.2, U2.4 (S2)
unnamed: R62.1, R46001.1, U3.1 (S1)
unnamed: R65.1, R46002.2, U3.4 (S2)
unnamed: R71.1, R47001.1, U4.1 (S1)
unnamed: R74.1, R47002.2, U4.4 (S2)
unnamed: C5001.2, R5002.2, U5001.3 (+)
unnamed: C8001.2, R8002.2, U8001.3 (+)
unnamed: C9001.2, R9002.2, U9001.3 (+)
unnamed: C15001.2, R15002.2, U15001.3 (+)
unnamed: C16001.2, R16002.2, U16001.3 (+)
unnamed: C17001.2, R17002.2, U17001.3 (+)
unnamed: C18001.2, R18002.2, U18001.3 (+)
unnamed: C20001.2, R20001.1, U20002.3 (+)
unnamed: C21001.2, R21002.2, U21001.3 (+)
unnamed: C24001.2, R24002.2, U24001.3 (+)
unnamed: C25001.2, R25002.2, U25001.3 (+)
unnamed: C30001.2, R30002.2, U28001.3 (+)
unnamed: C28003.2, R28002.2, U28002.3 (+)
unnamed: C32002.2, R32002.2, U30001.3 (+)
unnamed: C33002.2, R33002.2, U31001.3 (+)
unnamed: C44001.2, R44002.2, U42002.3 (+)
